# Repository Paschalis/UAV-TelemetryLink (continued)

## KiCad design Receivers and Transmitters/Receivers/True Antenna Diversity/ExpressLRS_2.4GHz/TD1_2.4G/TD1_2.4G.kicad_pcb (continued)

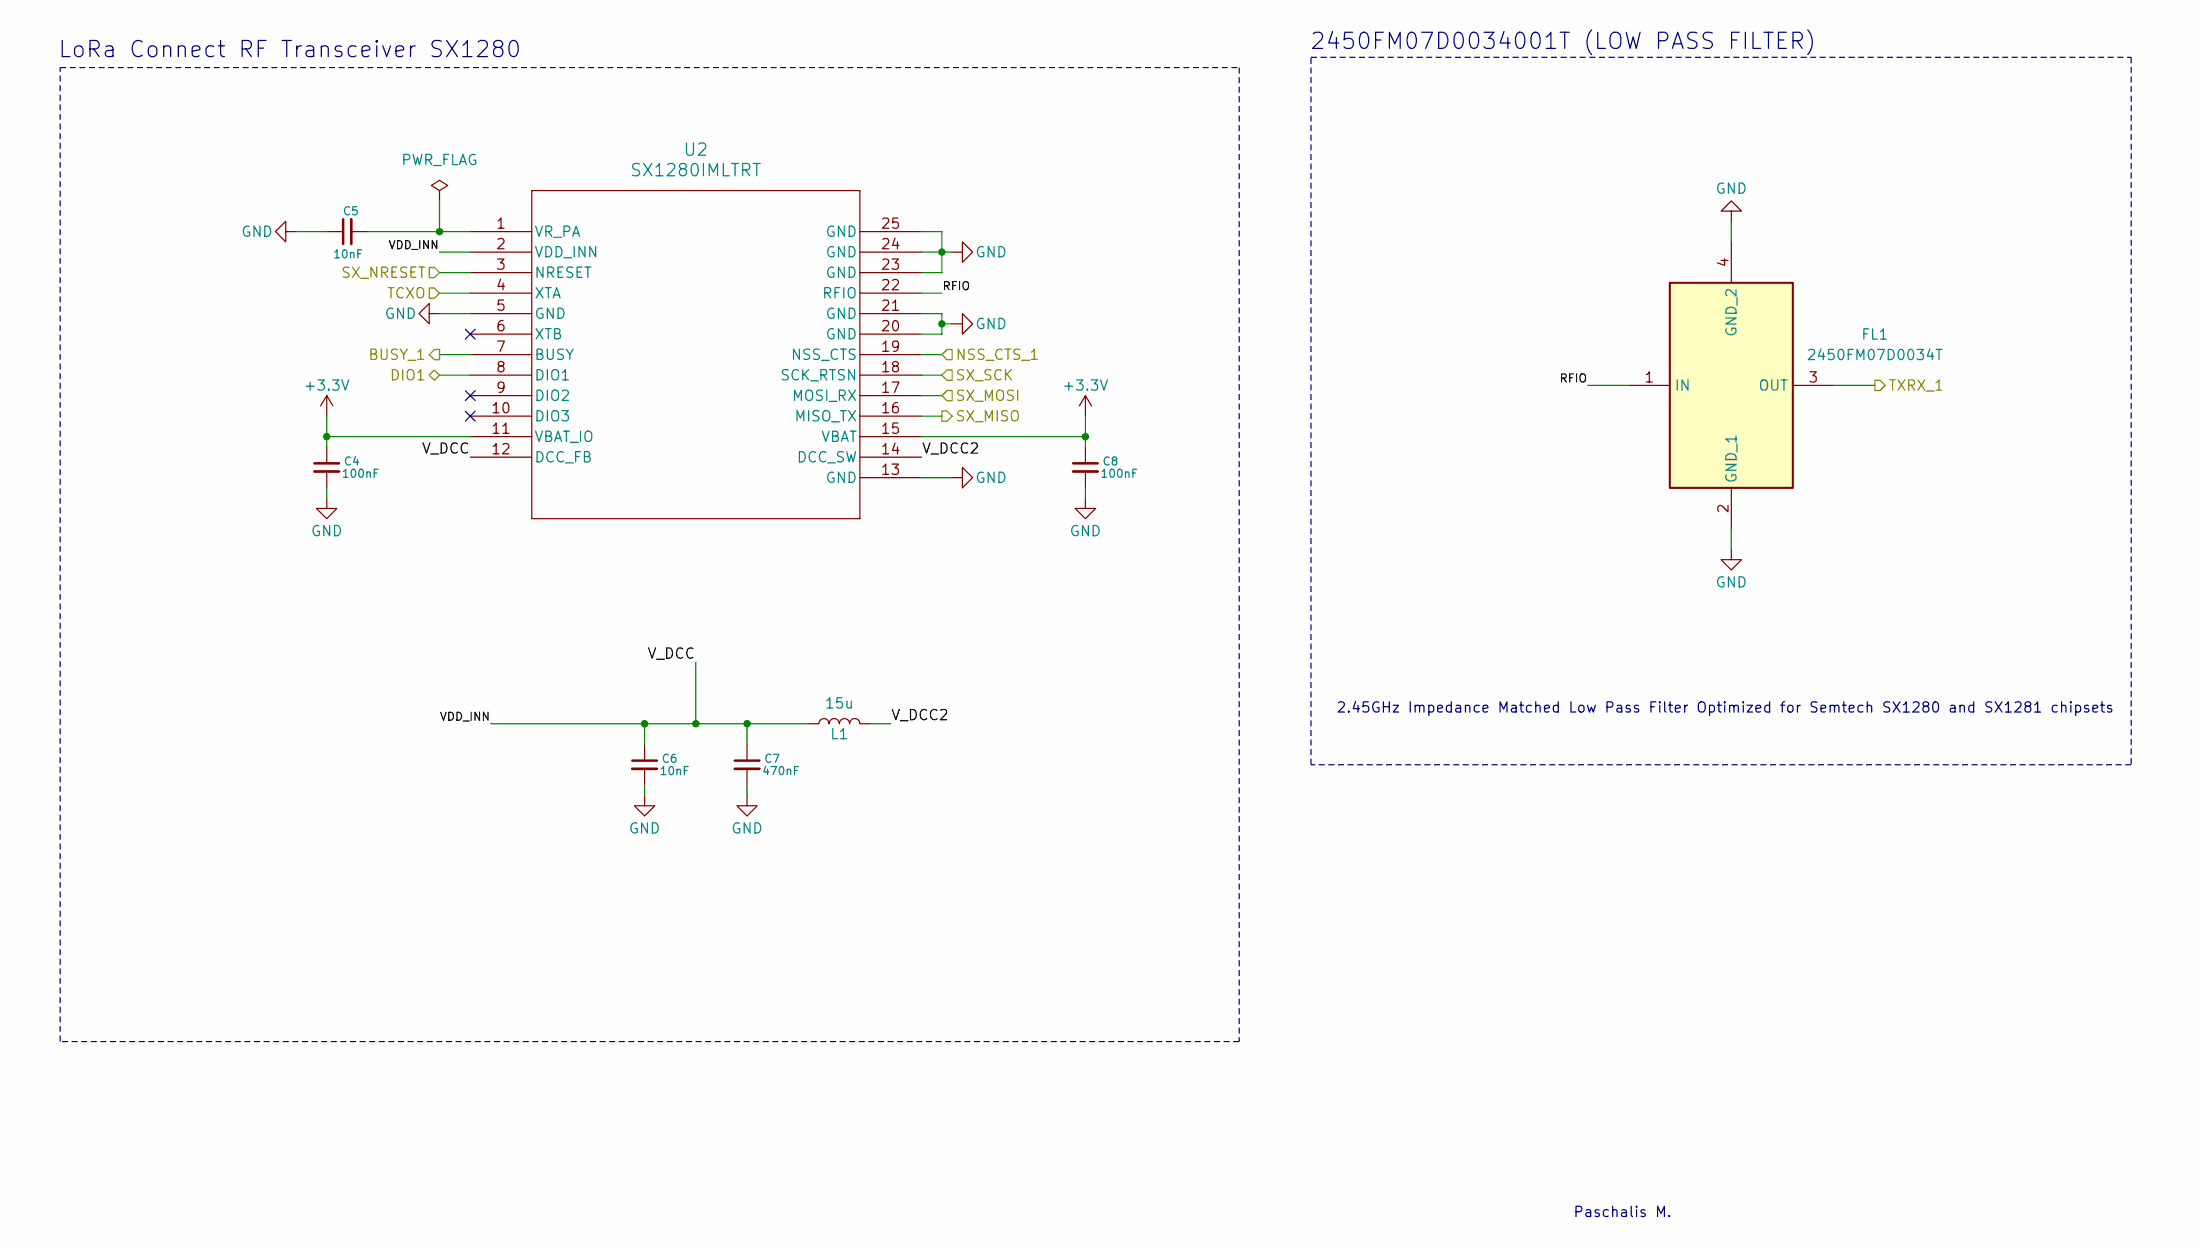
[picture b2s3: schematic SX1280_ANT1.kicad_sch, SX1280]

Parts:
C4, C8: 100nF; C_0603_1608Metric_Pad1.08x0.95mm_HandSolder
C5, C6: 10nF; C_0603_1608Metric_Pad1.08x0.95mm_HandSolder
C7: 470nF; C_0603_1608Metric_Pad1.08x0.95mm_HandSolder
FL1: 2450FM07D0034T; Mouser Part Number 609-2450FM07D0034T
L1: 15u; L_0805_2012Metric; LCSC C486333
U2: SX1280IMLTRT; QFN24_4X4_SEM

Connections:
+3.3V: C4.1, C8.1, U2.11 (VBAT_IO), U2.15 (VBAT); also elsewhere on the board
/BUSY_1: U2.7 (BUSY); also elsewhere on the board
/ESP32/DIO1: U2.8 (DIO1); also elsewhere on the board
/ESP32/NSS_CTS_1: U2.19 (NSS_CTS); also elsewhere on the board
/MISO: U2.16 (MISO_TX); also elsewhere on the board
/MOSI: U2.17 (MOSI_RX); also elsewhere on the board
/RESET: U2.3 (NRESET); also elsewhere on the board
/RFX2401C_ANT1/TXRX_1: FL1.3 (OUT); also elsewhere on the board
/SCK: U2.18 (SCK_RTSN); also elsewhere on the board
/SX1280_ANT1/RFIO: FL1.1 (IN), U2.22 (RFIO)
/SX1280_ANT1/VDD_INN: C6.1, C7.1, L1.1, U2.2 (VDD_INN), U2.12 (DCC_FB)
/SX1280_ANT1/V_DCC2: L1.2, U2.14 (DCC_SW)
/TCXO: U2.4 (XTA); also elsewhere on the board
GND: C4.2, C5.1, C6.2, C7.2, C8.2, FL1.2 (GND_1), FL1.4 (GND_2), U2.5 (GND), U2.13 (GND), U2.20 (GND), U2.21 (GND), U2.23 (GND), U2.24 (GND), U2.25 (GND); also elsewhere on the board
unnamed: C5.2, U2.1 (VR_PA)

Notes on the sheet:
LoRa Connect RF Transceiver SX1280
Paschalis M.
2.45GHz Impedance Matched Low Pass Filter Optimized for Semtech SX1280 and SX1281 chipsets
2450FM07D0034001T (LOW PASS FILTER)

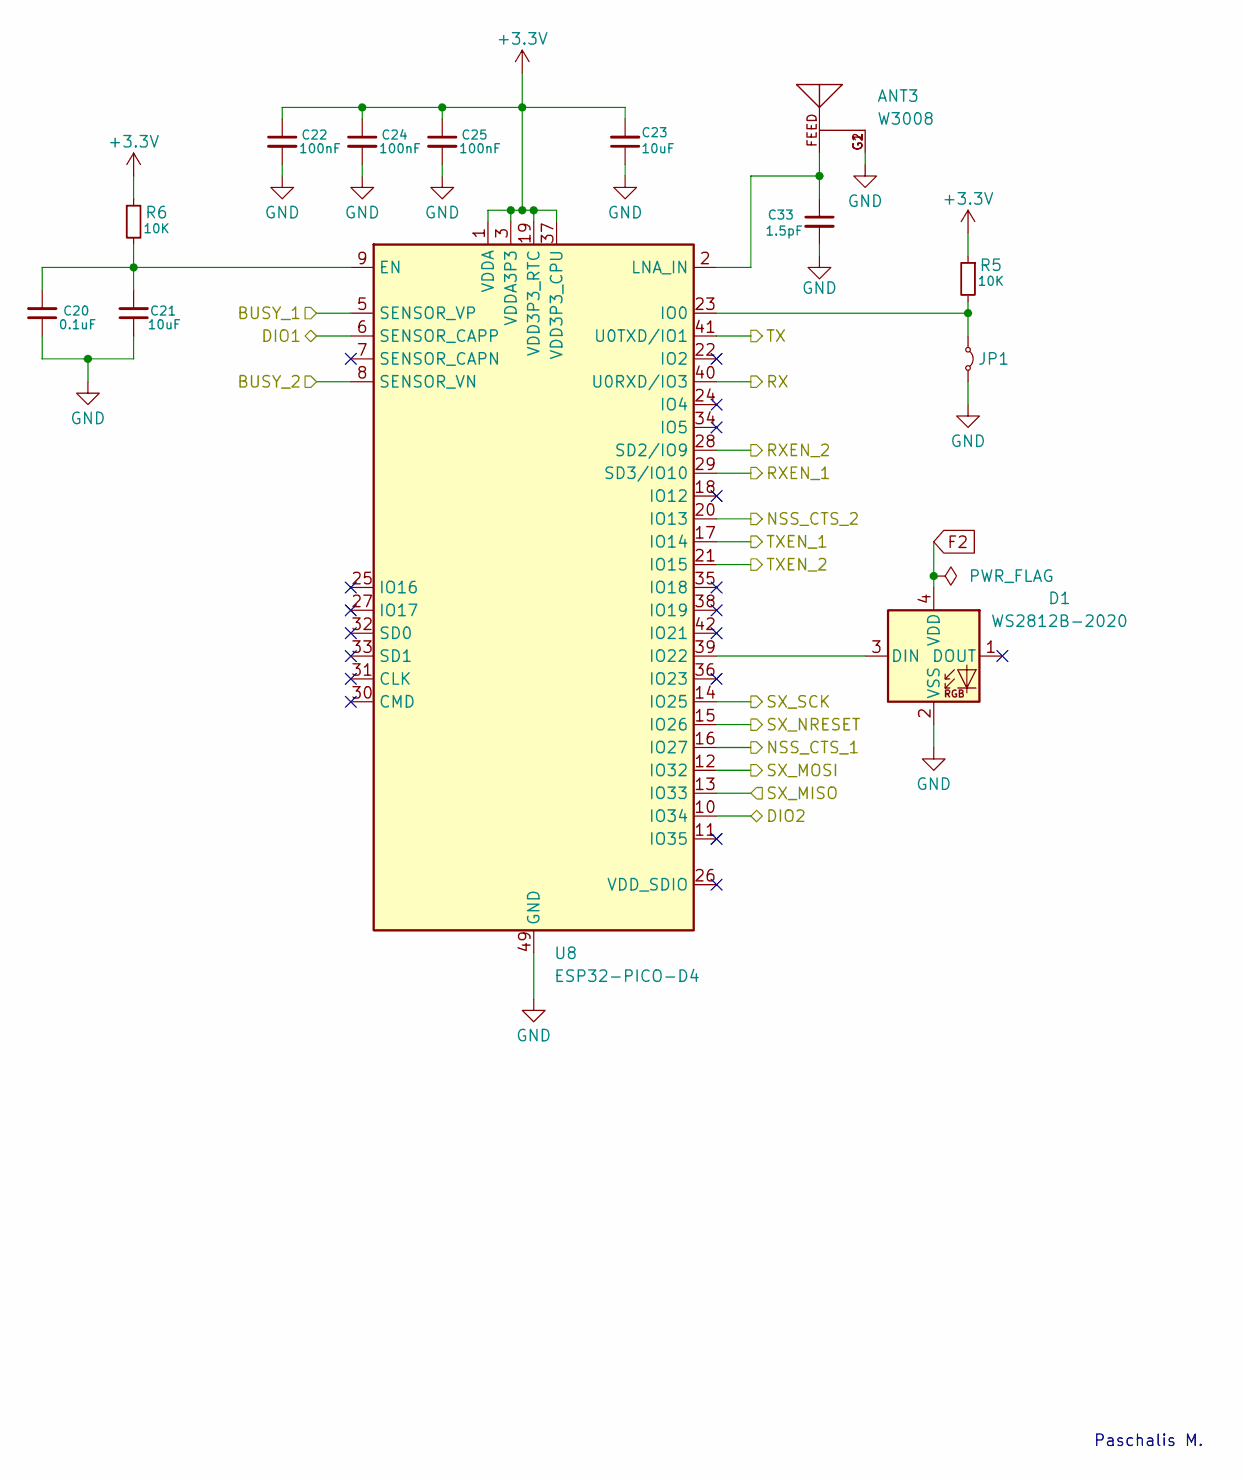
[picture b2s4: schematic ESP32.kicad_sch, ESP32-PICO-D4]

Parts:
ANT3: W3008; ANTENNA_W3008
C20: 0.1uF; C_0603_1608Metric_Pad1.08x0.95mm_HandSolder
C21, C23: 10uF; ECASD40J106M055K00
C22, C24, C25: 100nF; C_0603_1608Metric_Pad1.08x0.95mm_HandSolder
C33: 1.5pF; C_01005_0402Metric_Pad0.57x0.30mm_HandSolder
D1: WS2812B-2020; LED_WS2812B-2020_PLCC4_2.0x2.0mm
JP1: Jumper_2_Small_Bridged; TestPoint_2Pads_Pitch2.54mm_Drill0.8mm
R5, R6: 10K; R_0603_1608Metric_Pad0.98x0.95mm_HandSolder
U8: ESP32-PICO-D4; QFN-48-1EP_7x7mm_P0.5mm_EP5.1x5.1mm_ThermalVias

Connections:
+3.3V: C22.1, C23.2, C24.1, C25.1, R5.1, R6.1, U8.1 (VDDA), U8.3 (VDDA3P3), U8.4 (VDDA3P3), U8.19 (VDD3P3_RTC), U8.37 (VDD3P3_CPU), U8.43 (VDDA), U8.46 (VDDA); also elsewhere on the board
/BUSY_1: U8.5 (SENSOR_VP); also elsewhere on the board
/BUSY_2: U8.8 (SENSOR_VN); also elsewhere on the board
/ESP32/DIO1: U8.6 (SENSOR_CAPP); also elsewhere on the board
/ESP32/DIO2: U8.10 (IO34); also elsewhere on the board
/ESP32/NSS_CTS_1: U8.16 (IO27); also elsewhere on the board
/ESP32/NSS_CTS_2: U8.20 (IO13); also elsewhere on the board
/ESP32/RXEN_1: U8.29 (SD3/IO10); also elsewhere on the board
/ESP32/RXEN_2: U8.28 (SD2/IO9); also elsewhere on the board
/ESP32/TXEN_1: U8.17 (IO14); also elsewhere on the board
/ESP32/TXEN_2: U8.21 (IO15); also elsewhere on the board
/MISO: U8.13 (IO33); also elsewhere on the board
/MOSI: U8.12 (IO32); also elsewhere on the board
/RESET: U8.15 (IO26); also elsewhere on the board
/RX: U8.40 (U0RXD/IO3); also elsewhere on the board
/SCK: U8.14 (IO25); also elsewhere on the board
/TX: U8.41 (U0TXD/IO1); also elsewhere on the board
F2: D1.4 (VDD); also elsewhere on the board
GND: ANT3.G1, ANT3.G2, C20.1, C21.1, C22.2, C23.1, C24.2, C25.2, C33.2, D1.2 (VSS), JP1.2 (B), U8.49 (GND); also elsewhere on the board
unnamed: D1.3 (DIN), U8.39 (IO22)
unnamed: JP1.1 (A), R5.2, U8.23 (IO0)
unnamed: C20.2, C21.2, R6.2, U8.9 (EN)
unnamed: ANT3.FEED, C33.1, U8.2 (LNA_IN)

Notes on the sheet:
Paschalis M.

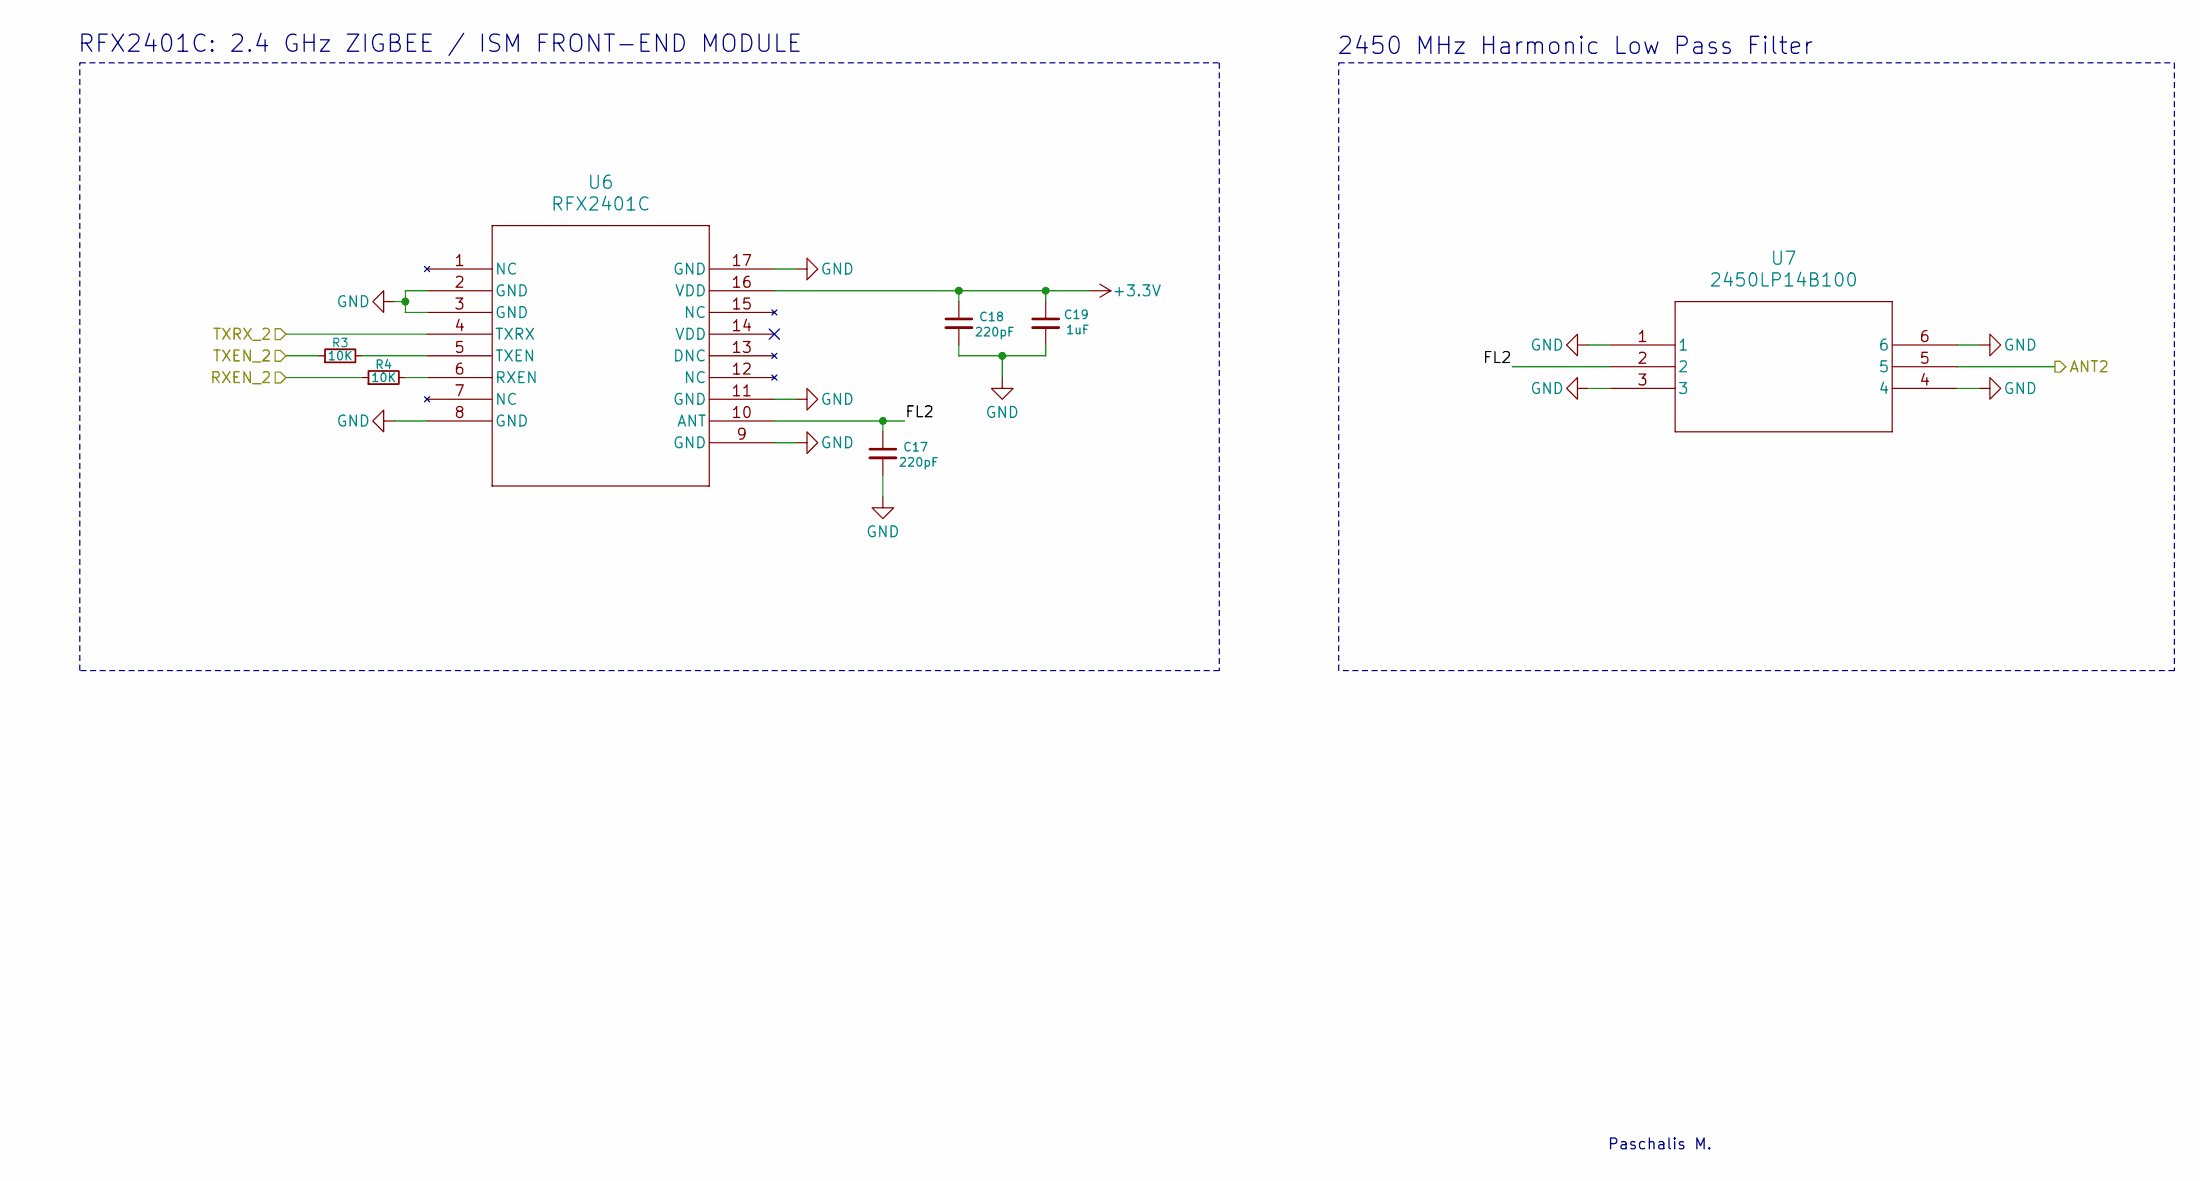
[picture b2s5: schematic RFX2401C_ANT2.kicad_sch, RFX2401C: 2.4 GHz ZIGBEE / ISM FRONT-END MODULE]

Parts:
C17, C18: 220pF; C_0603_1608Metric_Pad1.08x0.95mm_HandSolder
C19: 1uF; C_0603_1608Metric_Pad1.08x0.95mm_HandSolder
R3, R4: 10K; R_0603_1608Metric_Pad0.98x0.95mm_HandSolder
U6: RFX2401C; RFX2401C_SKY
U7: 2450LP14B100; CHIP_SMD_1P6XP8_JOD

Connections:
+3.3V: C18.1, C19.1, U6.16 (VDD); also elsewhere on the board
/ESP32/RXEN_2: R4.1; also elsewhere on the board
/ESP32/TXEN_2: R3.1; also elsewhere on the board
/RFX2401C_ANT2/ANT2: U7.5; also elsewhere on the board
/RFX2401C_ANT2/FL2: C17.1, U6.10 (ANT), U7.2
/RFX2401C_ANT2/TXRX_2: U6.4 (TXRX); also elsewhere on the board
GND: C17.2, C18.2, C19.2, U6.2 (GND), U6.3 (GND), U6.8 (GND), U6.9 (GND), U6.11 (GND), U6.17 (GND), U7.1, U7.3, U7.4, U7.6; also elsewhere on the board
unnamed: R4.2, U6.6 (RXEN)
unnamed: R3.2, U6.5 (TXEN)

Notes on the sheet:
RFX2401C: 2.4 GHz ZIGBEE / ISM FRONT-END MODULE
Paschalis M.
2450 MHz Harmonic Low Pass Filter

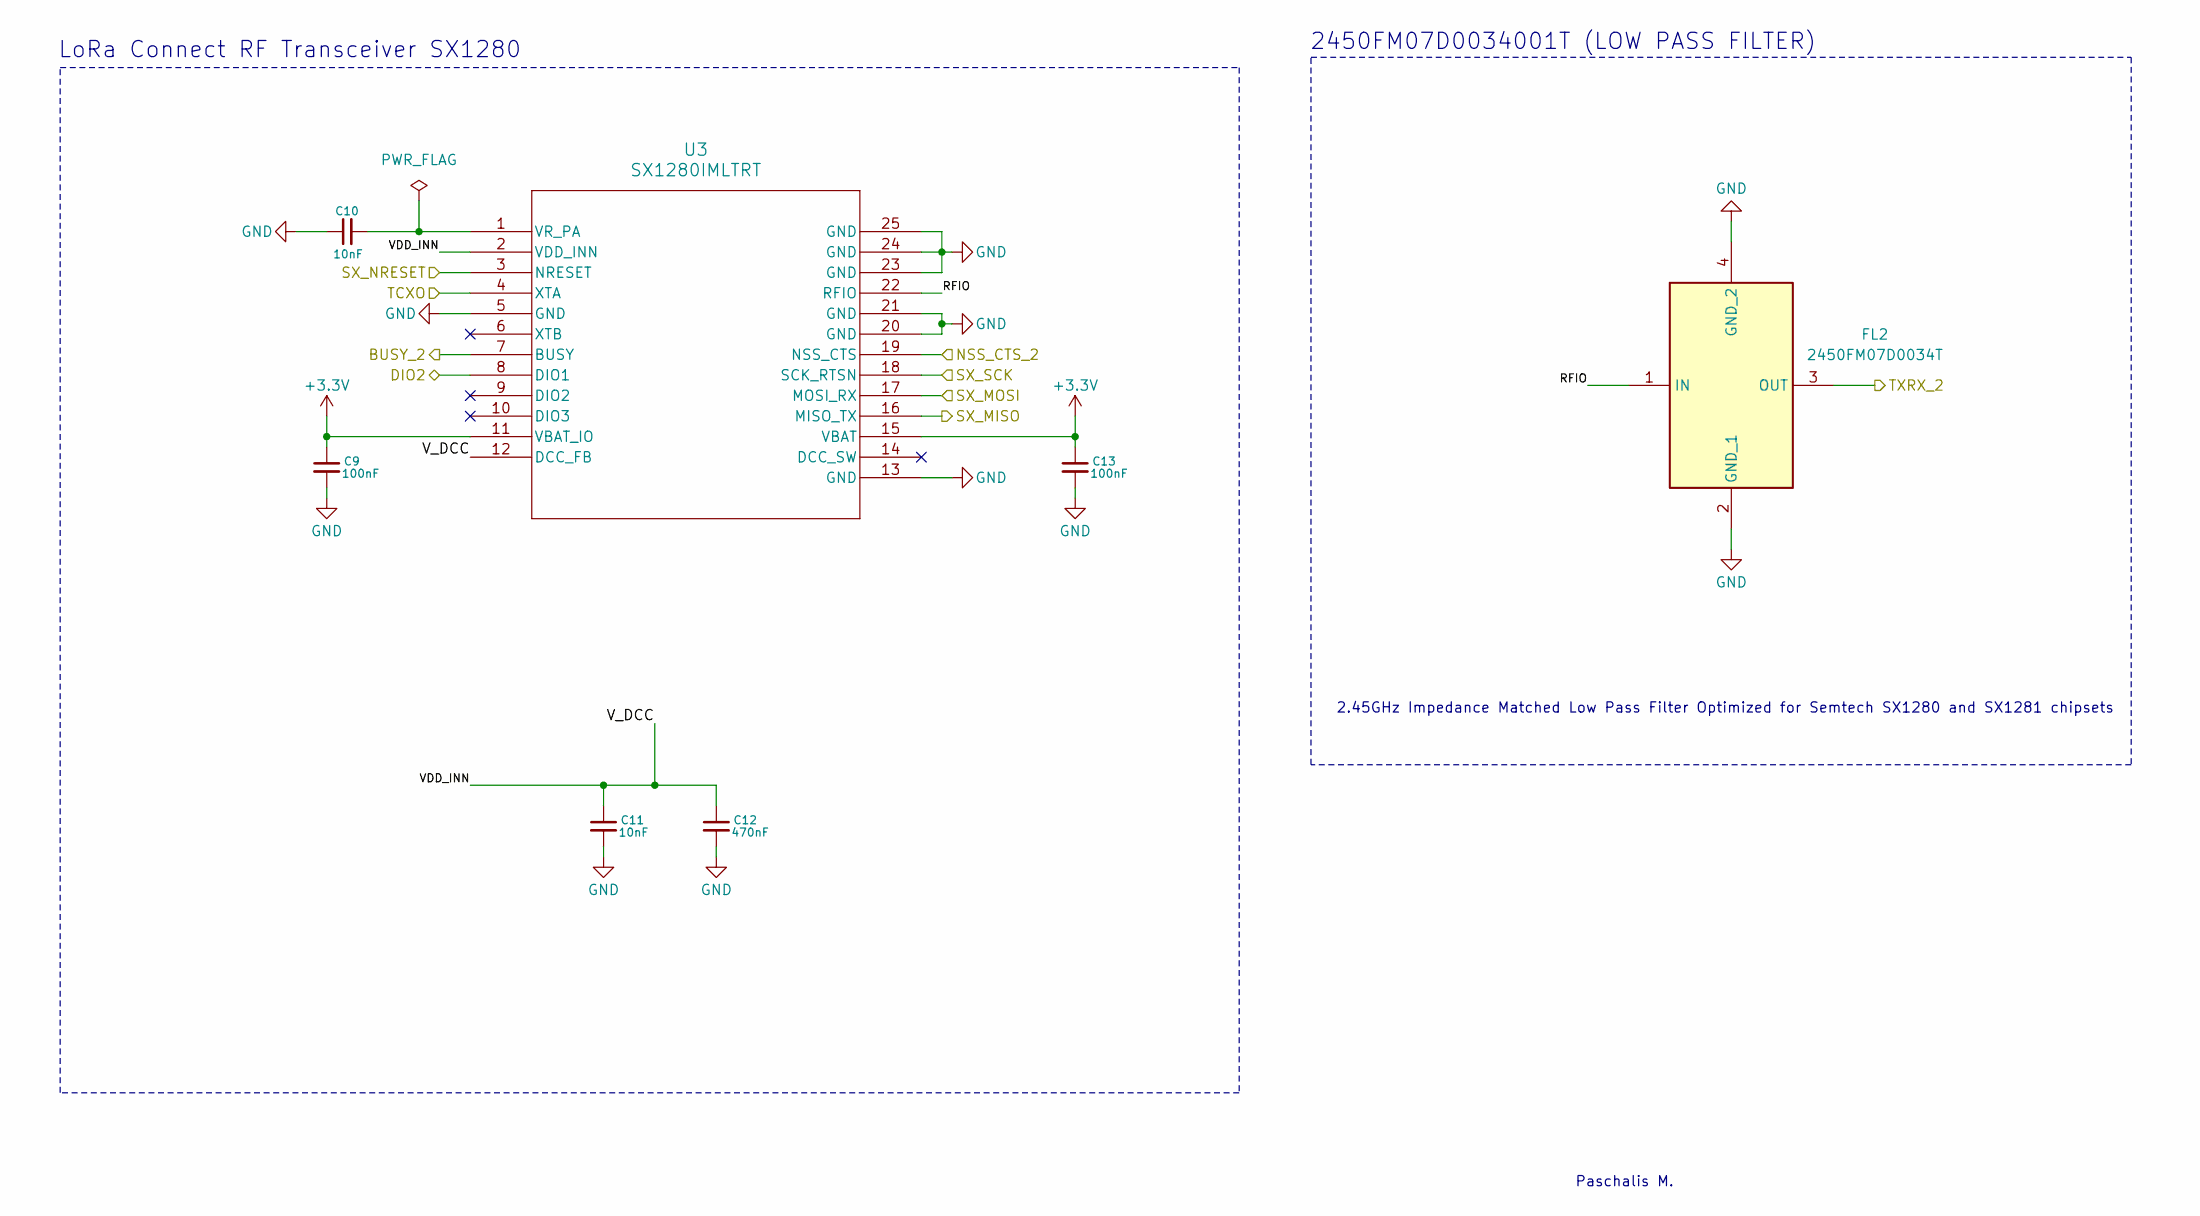
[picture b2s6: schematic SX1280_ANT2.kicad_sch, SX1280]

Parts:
C9, C13: 100nF; C_0603_1608Metric_Pad1.08x0.95mm_HandSolder
C10, C11: 10nF; C_0603_1608Metric_Pad1.08x0.95mm_HandSolder
C12: 470nF; C_0603_1608Metric_Pad1.08x0.95mm_HandSolder
FL2: 2450FM07D0034T; Mouser Part Number 609-2450FM07D0034T
U3: SX1280IMLTRT; QFN24_4X4_SEM

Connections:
+3.3V: C9.1, C13.1, U3.11 (VBAT_IO), U3.15 (VBAT); also elsewhere on the board
/BUSY_2: U3.7 (BUSY); also elsewhere on the board
/ESP32/DIO2: U3.8 (DIO1); also elsewhere on the board
/ESP32/NSS_CTS_2: U3.19 (NSS_CTS); also elsewhere on the board
/MISO: U3.16 (MISO_TX); also elsewhere on the board
/MOSI: U3.17 (MOSI_RX); also elsewhere on the board
/RESET: U3.3 (NRESET); also elsewhere on the board
/RFX2401C_ANT2/TXRX_2: FL2.3 (OUT); also elsewhere on the board
/SCK: U3.18 (SCK_RTSN); also elsewhere on the board
/SX1280_ANT2/RFIO: FL2.1 (IN), U3.22 (RFIO)
/SX1280_ANT2/VDD_INN: C11.1, C12.1, U3.2 (VDD_INN), U3.12 (DCC_FB)
/TCXO: U3.4 (XTA); also elsewhere on the board
GND: C9.2, C10.1, C11.2, C12.2, C13.2, FL2.2 (GND_1), FL2.4 (GND_2), U3.5 (GND), U3.13 (GND), U3.20 (GND), U3.21 (GND), U3.23 (GND), U3.24 (GND), U3.25 (GND); also elsewhere on the board
unnamed: C10.2, U3.1 (VR_PA)

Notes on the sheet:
LoRa Connect RF Transceiver SX1280
Paschalis M.
2450FM07D0034001T (LOW PASS FILTER)
2.45GHz Impedance Matched Low Pass Filter Optimized for Semtech SX1280 and SX1281 chipsets

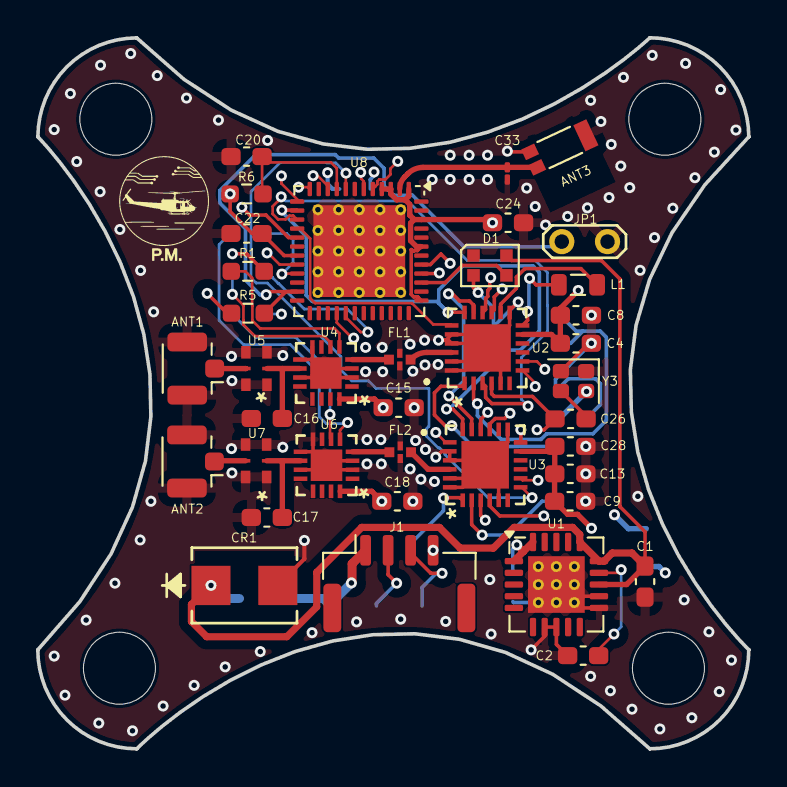
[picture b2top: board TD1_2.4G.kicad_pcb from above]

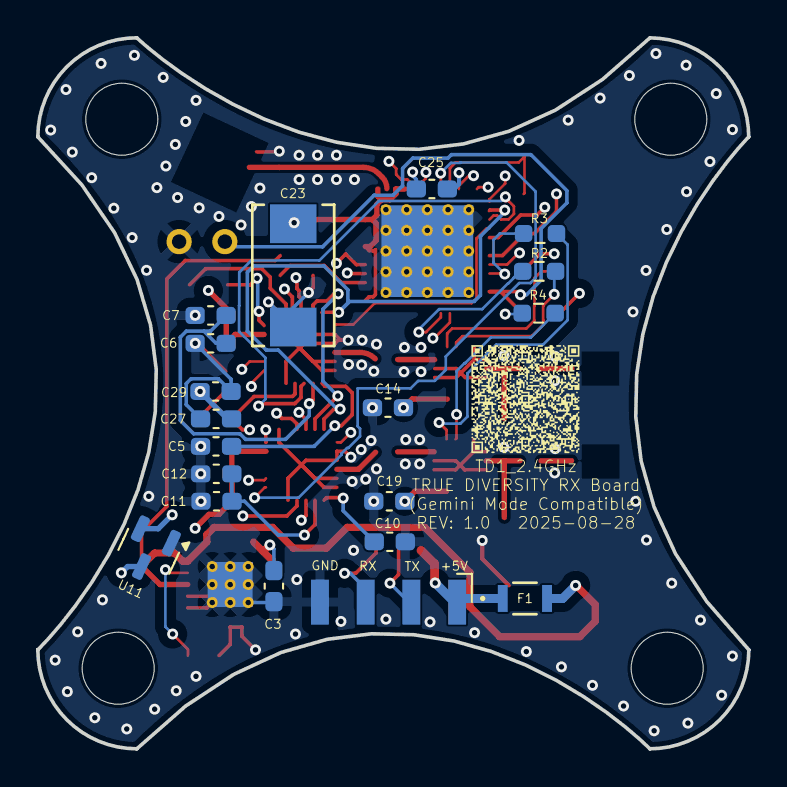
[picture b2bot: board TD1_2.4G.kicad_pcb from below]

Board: 6 copper layers, 39.5 x 39.5 mm, 61 parts (19 on the bottom side), 45 nets.

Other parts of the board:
Hole3, Hole4: (no value)
hole1, hole2: (no value)

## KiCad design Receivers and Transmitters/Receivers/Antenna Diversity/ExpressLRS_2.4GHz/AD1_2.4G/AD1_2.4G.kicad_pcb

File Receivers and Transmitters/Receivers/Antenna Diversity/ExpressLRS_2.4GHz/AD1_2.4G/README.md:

<div align="center">

# AD1_2.4G

Antenna Diversity 
(Basic diversity setup)

</div>

<p align="center"> or </p>  <p align="center">Click the icons to open iBOM or KiCanvas</p> 

## Bill of Materials

| **Reference** | **Value**         | **Datasheet** | **Footprint** | **Qty** | **DNP** |
|--------------|------------------|--------------|-------------|------|------|
| AE1         | Antenna          | ~            | RF_Antenna:Texas_SWRA117D_2.4GHz_Right | 1  |      |
| ANT1, ANT2  | Conn_Coaxial     | ~            | Connector_Coaxial:U.FL_Hirose_U.FL-R-SMT-1_Vertical | 2  |      |
| C1, C30, C32 | 10uF            | ~            | Capacitor_SMD:C_0805_2012Metric_Pad1.18x1.45mm_HandSolder,ECASD40J106M055K00:ECASD40J106M055K00 | 3  |      |
| C2          | 1uF             | ~            | Capacitor_SMD:C_0805_2012Metric_Pad1.18x1.45mm_HandSolder | 1  |      |
| C3          | 47uF            | ~            | Capacitor_SMD:C_0805_2012Metric_Pad1.18x1.45mm_HandSolder | 1  |      |
| C4          | 2.2uF           | ~            | Capacitor_SMD:C_0805_2012Metric_Pad1.18x1.45mm_HandSolder | 1  |      |
| C5, C6, C21, C22 | 10pF       | ~            | Capacitor_SMD:C_0805_2012Metric_Pad1.18x1.45mm_HandSolder | 4  |      |
| C7, C16, C17, C23, C24, C25, C26, C27, C28, C29 | 100nF | ~ | Capacitor_SMD:C_0805_2012Metric_Pad1.18x1.45mm_HandSolder | 10 |      |
| C18         | 470nF           | ~            | Capacitor_SMD:C_0805_2012Metric_Pad1.18x1.45mm_HandSolder | 1  |      |
| C19, C20    | 10nF            | ~            | Capacitor_SMD:C_0805_2012Metric_Pad1.18x1.45mm_HandSolder | 2  |      |
| C31         | 0.1uF           | ~            | Capacitor_SMD:C_0805_2012Metric_Pad1.18x1.45mm_HandSolder | 1  |      |
| D1          | LED             | ~            | LED_SMD:LED_0805_2012Metric_Pad1.15x1.40mm_HandSolder | 1  |      |
| FL1         | 2450FM07D0034T  | [Datasheet](https://www.mouser.co.uk/datasheet/2/611/2450FM07D0034-1375634.pdf) | 2450FM07D0034T:2450FM07D0034T | 1 |      |
| J1          | Conn_01x04_Socket | ~           | Connector_Harwin:Harwin_M20-89004xx_1x04_P2.54mm_Horizontal | 1  |      |
| J3          | Conn_01x04_Pin  | ~            | Connector_JST:JST_GH_SM04B-GHS-TB_1x04-1MP_P1.25mm_Horizontal | 1  |      |
| JP1         | Jumper_2_Bridged | ~            | TestPoint:TestPoint_2Pads_Pitch2.54mm_Drill0.8mm | 1  |      |
| R1          | 2.2K            | ~            | Resistor_SMD:R_0805_2012Metric_Pad1.20x1.40mm_HandSolder | 1  |      |
| R2, R3, R7, R8, R10 | 10K     | ~            | Resistor_SMD:R_0805_2012Metric_Pad1.20x1.40mm_HandSolder | 5  |      |
| R4          | 12K             | ~            | Resistor_SMD:R_0805_2012Metric_Pad1.20x1.40mm_HandSolder | 1  |      |
| R5          | 0               | ~            | Resistor_SMD:R_0805_2012Metric_Pad1.20x1.40mm_HandSolder | 1  |      |
| R6          | 1K              | ~            | Resistor_SMD:R_0805_2012Metric_Pad1.20x1.40mm_HandSolder | 1  |      |
| R9          | 1.2K            | ~            | Resistor_SMD:R_0805_2012Metric_Pad1.20x1.40mm_HandSolder | 1  |      |
| U1          | TPS7A4701xRGW   | [Datasheet](https://www.ti.com/lit/ds/symlink/tps7a47.pdf) | Package_DFN_QFN:Texas_RGW0020A_VQFN-20-1EP_5x5mm_P0.65mm_EP3.15x3.15mm_ThermalVias | 1 |      |
| U2          | SX1280IMLTRT    | SX1280IMLTRT | SX1280IMLTRT:QFN24_4X4_SEM | 1 |      |
| U3          | ESP8285H16      | ESP8285H16   | ESP8285H16:QFN32_5X5_EXP | 1 |      |
| U4          | SE2431L-R       | SE2431L-R    | SE2431L-R:SE2431L_SKY | 1 |      |
| Y1          | 52MHz           | ~            | Crystal:Crystal_SMD_2016-4Pin_2.0x1.6mm | 1 |      |
| Y2          | 26MHz           | ~            | Crystal:Crystal_SMD_2016-4Pin_2.0x1.6mm | 1 |      |

[⬅️ Go Back to Main README](https://github.com/Paschalis/UAV-TelemetryLink)

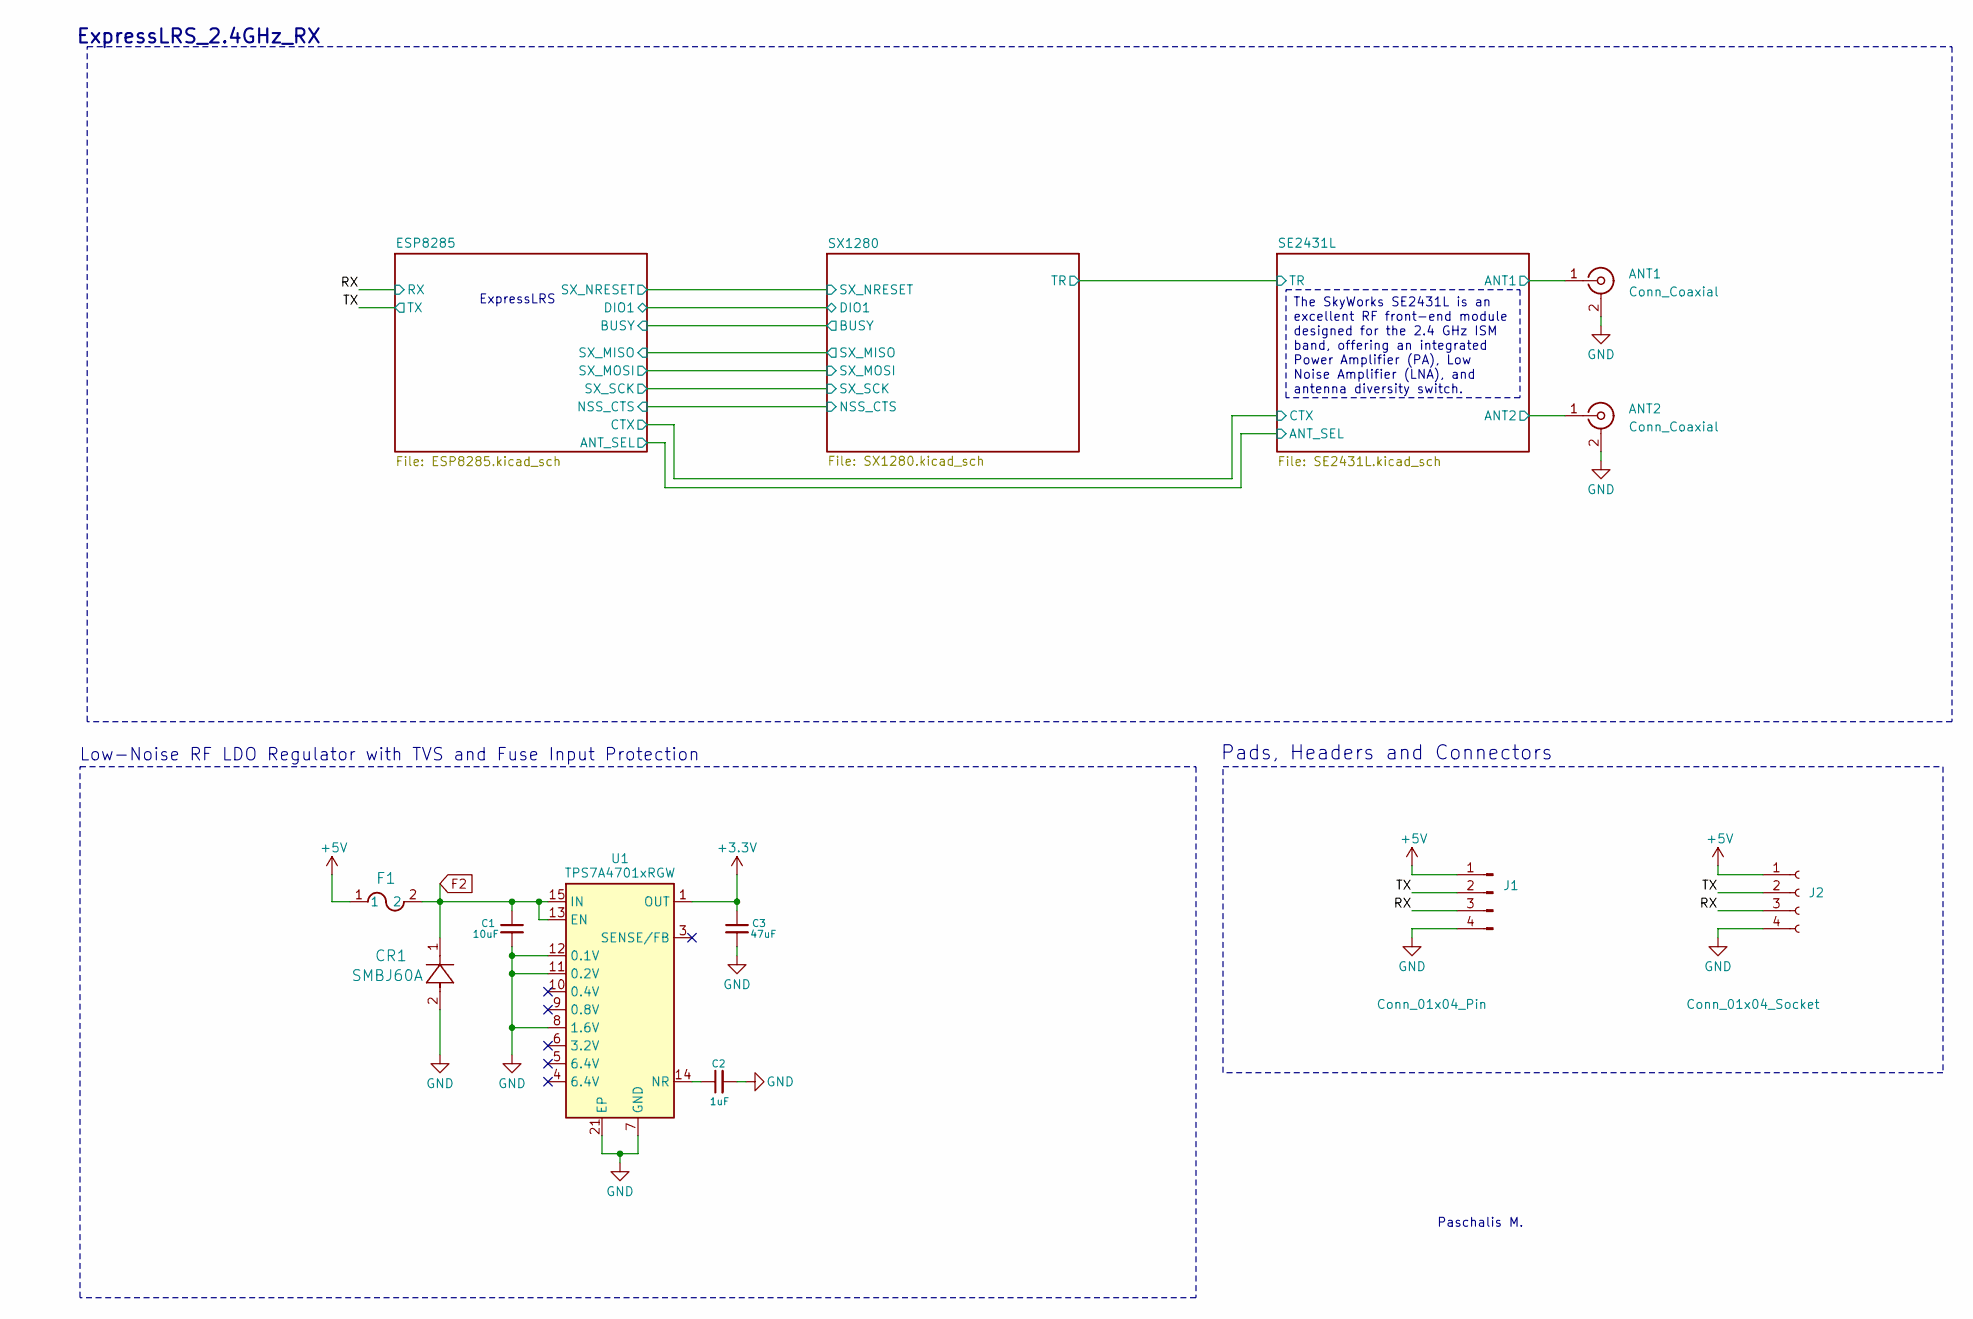
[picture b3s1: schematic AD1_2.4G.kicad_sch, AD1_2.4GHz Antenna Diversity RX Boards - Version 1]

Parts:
ANT1, ANT2: Conn_Coaxial; U.FL_Hirose_U.FL-R-SMT-1_Vertical
C1: 10uF; C_0603_1608Metric_Pad1.08x0.95mm_HandSolder
C2: 1uF; C_0603_1608Metric_Pad1.08x0.95mm_HandSolder
C3: 47uF; C_0603_1608Metric_Pad1.08x0.95mm_HandSolder
CR1: SMBJ60A; SMBJSeries_LTF
F1: MF-PSMF020X-2; FUSE_F020X_BRN
J1: Conn_01x04_Pin; JST_GH_SM04B-GHS-TB_1x04-1MP_P1.25mm_Horizontal
J2: Conn_01x04_Socket; Harwin_M20-89004xx_1x04_P2.54mm_Horizontal
U1: TPS7A4701xRGW; Texas_RGW0020A_VQFN-20-1EP_5x5mm_P0.65mm_EP3.15x3.15mm_Ther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

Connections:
+3.3V: C3.1, U1.1 (OUT), U1.20 (OUT); also elsewhere on the board
+5V: F1.1, J1.1, J2.1
/RX: J1.3, J2.3; also elsewhere on the board
/SE2431L/ANT1: ANT1.1 (In); also elsewhere on the board
/SE2431L/ANT2: ANT2.1 (In); also elsewhere on the board
/TX: J1.2, J2.2; also elsewhere on the board
F2: C1.1, CR1.1, F1.2, U1.13 (EN), U1.15 (IN), U1.16 (IN)
GND: ANT1.2 (Ext), ANT2.2 (Ext), C1.2, C2.2, C3.2, CR1.2, J1.4, J2.4, U1.7 (GND), U1.8 (1.6V), U1.11 (0.2V), U1.12 (0.1V), U1.21 (EP); also elsewhere on the board
unnamed: C2.1, U1.14 (NR)

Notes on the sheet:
ExpressLRS
Pads, Headers and Connectors
Paschalis M.
Low-Noise RF LDO Regulator with TVS and Fuse Input Protection
ExpressLRS_2.4GHz_RX
The SkyWorks SE2431L is an excellent RF front-end module designed for the 2.4 GHz ISM band, offering an integrated Power Amplifier (PA), Low Noise Amplifier (LNA), and antenna diversity switch.

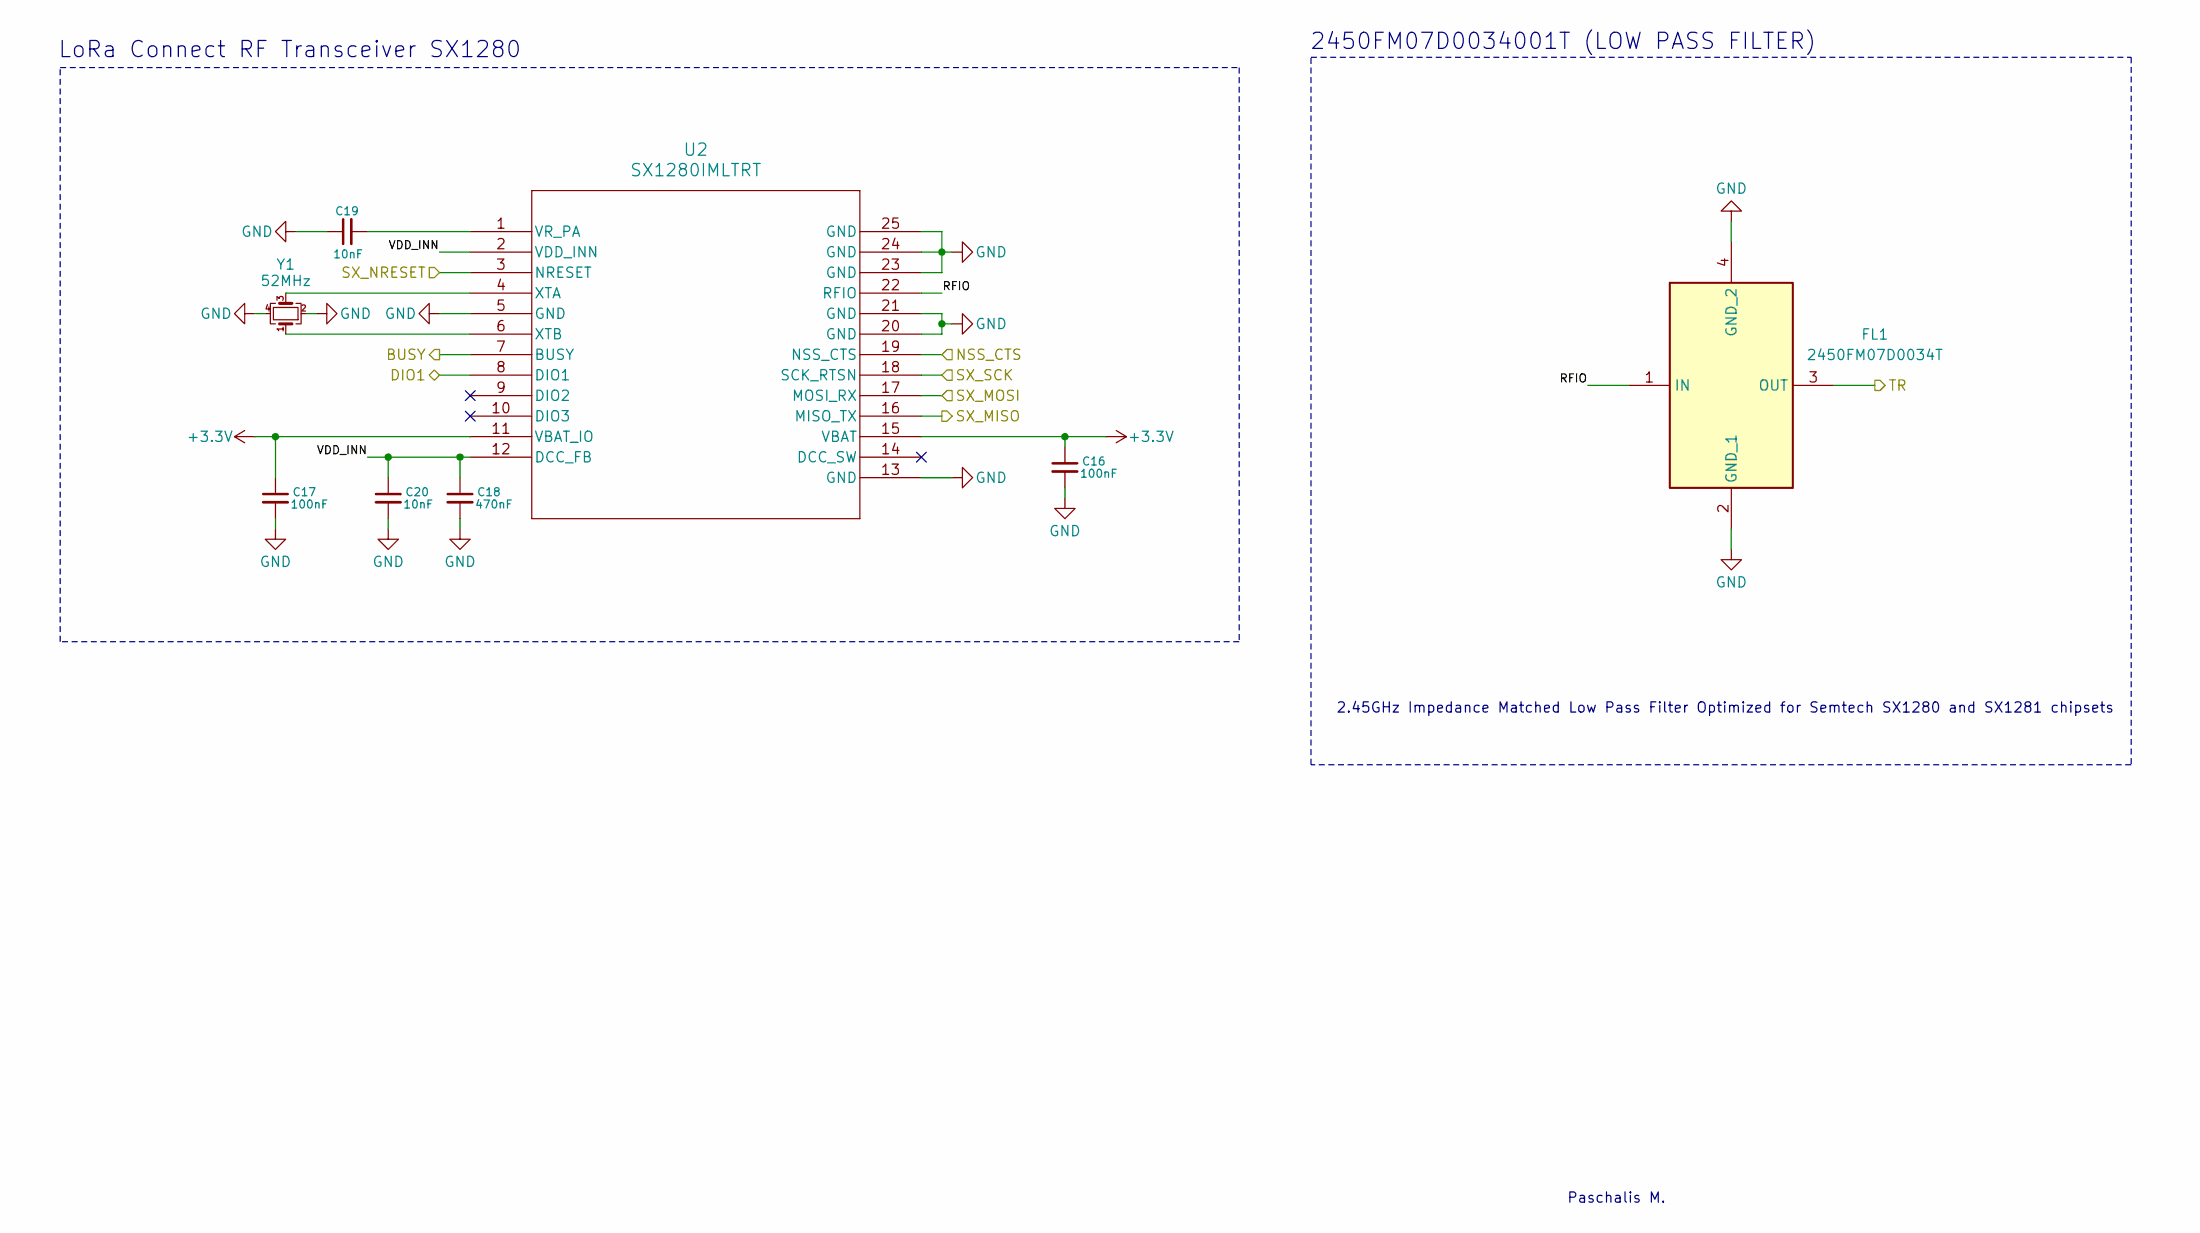
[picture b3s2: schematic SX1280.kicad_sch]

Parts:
C16, C17: 100nF; C_0603_1608Metric_Pad1.08x0.95mm_HandSolder
C18: 470nF; C_0603_1608Metric_Pad1.08x0.95mm_HandSolder
C19, C20: 10nF; C_0603_1608Metric_Pad1.08x0.95mm_HandSolder
FL1: 2450FM07D0034T; Mouser Part Number 609-2450FM07D0034T
U2: SX1280IMLTRT; QFN24_4X4_SEM
Y1: 52MHz; Crystal_SMD_2016-4Pin_2.0x1.6mm

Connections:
+3.3V: C16.1, C17.1, U2.11 (VBAT_IO), U2.15 (VBAT); also elsewhere on the board
/ESP8285/BUSY: U2.7 (BUSY); also elsewhere on the board
/ESP8285/DIO1: U2.8 (DIO1); also elsewhere on the board
/ESP8285/NSS_CTS: U2.19 (NSS_CTS); also elsewhere on the board
/ESP8285/SX_MISO: U2.16 (MISO_TX); also elsewhere on the board
/ESP8285/SX_MOSI: U2.17 (MOSI_RX); also elsewhere on the board
/ESP8285/SX_NRESET: U2.3 (NRESET); also elsewhere on the board
/ESP8285/SX_SCK: U2.18 (SCK_RTSN); also elsewhere on the board
/SE2431L/TR: FL1.3 (OUT); also elsewhere on the board
/SX1280/RFIO: FL1.1 (IN), U2.22 (RFIO)
/SX1280/VDD_INN: C18.1, C20.1, U2.2 (VDD_INN), U2.12 (DCC_FB)
GND: C16.2, C17.2, C18.2, C19.1, C20.2, FL1.2 (GND_1), FL1.4 (GND_2), U2.5 (GND), U2.13 (GND), U2.20 (GND), U2.21 (GND), U2.23 (GND), U2.24 (GND), U2.25 (GND), Y1.2, Y1.4; also elsewhere on the board
unnamed: C19.2, U2.1 (VR_PA)
unnamed: U2.4 (XTA), Y1.3
unnamed: U2.6 (XTB), Y1.1

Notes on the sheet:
2.45GHz Impedance Matched Low Pass Filter Optimized for Semtech SX1280 and SX1281 chipsets
2450FM07D0034001T (LOW PASS FILTER)
Paschalis M.
LoRa Connect RF Transceiver SX1280
